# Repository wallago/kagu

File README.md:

# Kagu

A wireless 36-key split keyboard (3x5+3) on the Seeed XIAO nRF52840, running ZMK.

- `keymap.txt`: the keymap, the only file to edit for layout changes
- `keymap/`: the generator that turns it into ZMK, and the diagram
- `config/`: ZMK shields and the generated `kagu.keymap`
- `pcb/`: KiCad projects for both halves
- `case/`: OpenSCAD trays, top plates and Choc v2 keycap risers

## Layout

Colemak-DH, after [dubu36](https://github.com/denniskempin/dubu36). Shortcut modifiers sit on the
home row (pinky to index: Shift, Ctrl, Alt, Super, mirrored). Shift and the layers you use while
writing sit on the thumbs, which keeps hold-tap timing out of the way. Some notes on the layers:

- **rse**: numbers on the left, navigation on the right. **lwr**: symbols.
- **app** and **os**: held from C and `,` (app) or D and H (os). They keep Ctrl or Super down for
  the whole hold, so every key is sent with that modifier, including the arrows on U N E I.
- **sys**: Bluetooth profiles, held from Z or `/`.
- **mou**: held from X. Left-hand Ctrl+Q W S T Z C V for when the right hand is on the mouse.
- **hyp**: held from the right outer thumb. Every key is sent with Ctrl+Alt+Shift+Super, for niri
  bindings. The HYP_[ HYP_\ HYP_] keys on rse send the same.
- Combos: W+F types Esc, and U+Y types Enter.

## Editing the keymap

Each layer is a grid of the 36 keys, laid out as they sit on the board: three rows of ten, then
the six thumbs.

```
layer base: left_mods, right_mods
  Q      W        F      P     B          J        L     U      Y     '
  A      R        S      T     G          M        N     E      I     O
  Z/sys  X/mou    C/app  D/os  V          K        H/os  ,/app  .     \//sys
                  BSPC   LSHFT/LSHFT  lwr/lwr     rse/rse  SPC   _/hyp
```

```
  Z/sys         tap Z, hold the sys layer
  T/LGUI:hm     tap T, hold Super, as a positional home-row mod
  LSHFT/LSHFT   one-shot Shift on tap, plain Shift on hold
  _ / TRNS      nothing / fall through to the layer below
```

Holds shared by several layers are written once as an `overlay` and listed after the layer name.
`layer app + LCTRL` holds Ctrl for as long as the layer is held. Combos are written
`W F -> ESC`. The header of `keymap.txt` covers the details.

After editing, run `just keymap` in the Nix dev shell. It regenerates `kagu.keymap` and redraws
the diagram with [keymap-drawer](https://github.com/caksoylar/keymap-drawer). CI fails if
`kagu.keymap` is out of date.

## Keycaps

- [3dkeycap.com](https://3dkeycap.com)

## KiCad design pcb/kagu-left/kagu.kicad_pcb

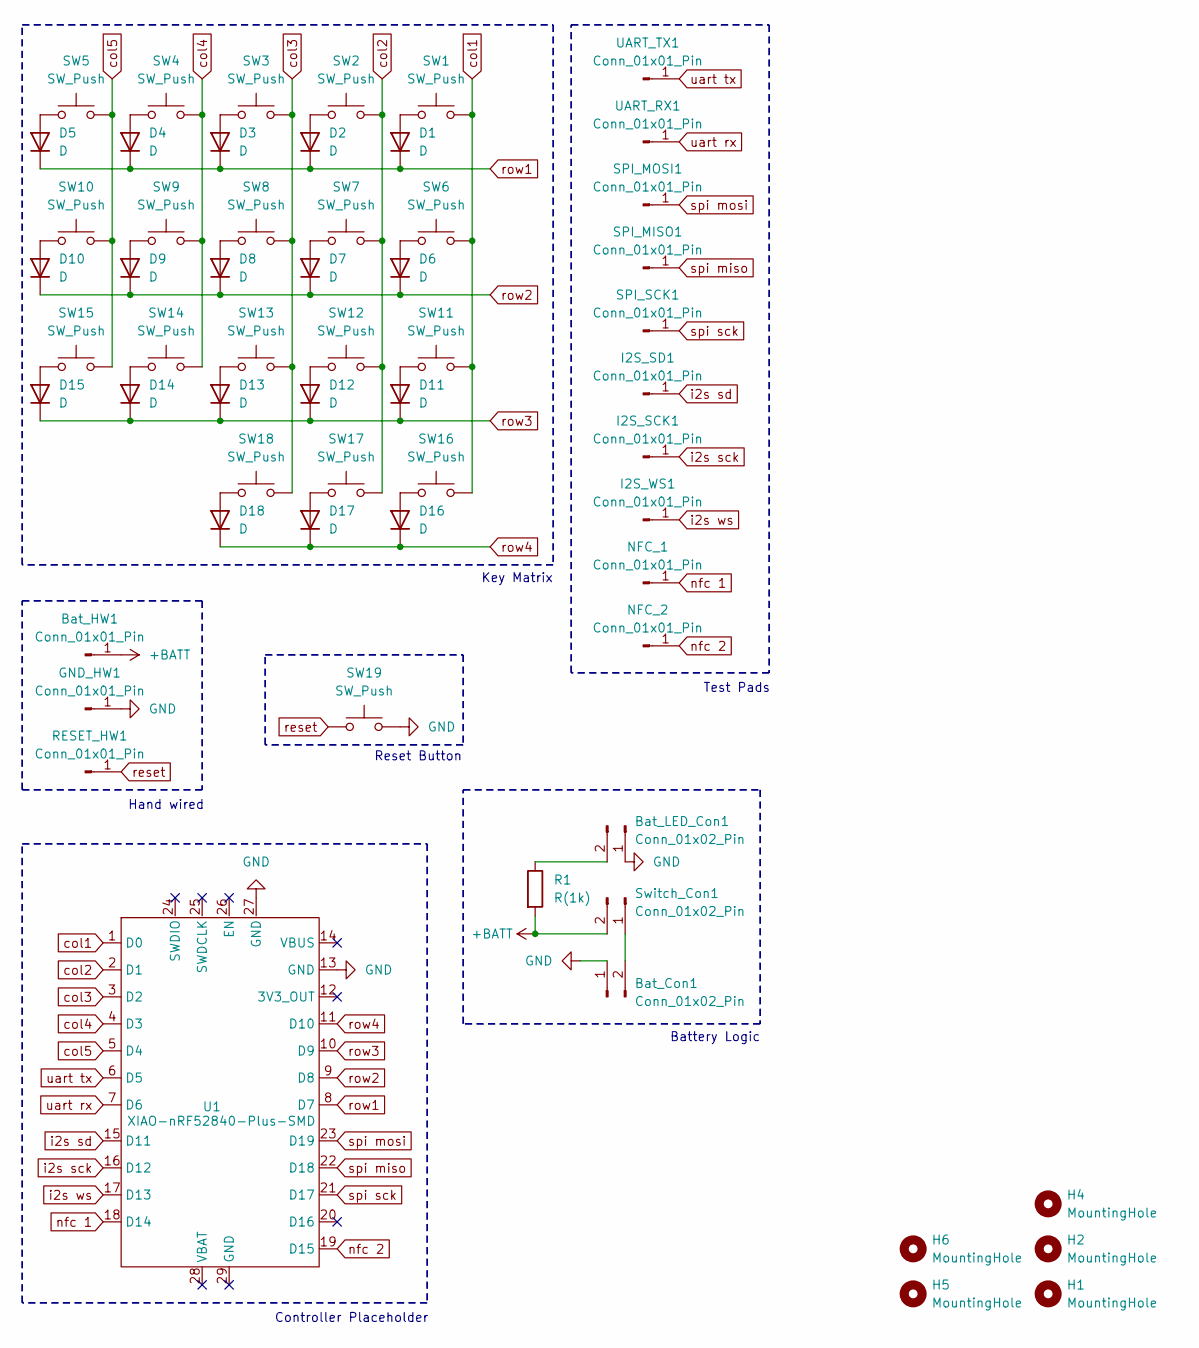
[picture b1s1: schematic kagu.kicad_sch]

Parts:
Bat_Con1: Conn_01x02_Pin; JST_PH_S2B-PH-SM4-TB_1x02-1MP_P2.00mm_Horizontal
Bat_HW1: Conn_01x01_Pin; TestPad
Bat_LED_Con1: Conn_01x02_Pin; JST_SH_SM02B-SRSS-TB_1x02-1MP_P1.00mm_Horizontal
D1, D2, D3, D4, D5, D6, D7, D8, D9, D10, D11, D12, D13, D14, D15, D16, D17, D18: D; D_SOD-123
GND_HW1: Conn_01x01_Pin; TestPad
H1, H2, H4, H5, H6: MountingHole; MountingHole_3.2mm_M3_DIN965_Pad
I2S_SCK1, I2S_SD1, I2S_WS1: Conn_01x01_Pin; TestPad
NFC_1, NFC_2: Conn_01x01_Pin; TestPad
R1: R(1k); R_0805_2012Metric
RESET_HW1: Conn_01x01_Pin; TestPad
SPI_MISO1: Conn_01x01_Pin; TestPad
SPI_MOSI1: Conn_01x01_Pin; TestPad
SPI_SCK1: Conn_01x01_Pin; TestPad
SW1, SW2, SW3, SW4, SW5, SW6, SW7, SW8, SW9, SW10, SW11, SW12, SW13, SW14, SW15, SW16, SW17, SW18: SW_Push; SW_Hotswap_Kailh_Choc_V1V2_Plated
SW19: SW_Push; SW_Push_SPST_NO_Alps_SKRK
Switch_Con1: Conn_01x02_Pin; JST_PH_S2B-PH-SM4-TB_1x02-1MP_P2.00mm_Horizontal
U1: XIAO-nRF52840-Plus-SMD; XIAO-23P-Add-On-Plus
UART_RX1: Conn_01x01_Pin; TestPad
UART_TX1: Conn_01x01_Pin; TestPad

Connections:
+BATT: Bat_HW1.1 (Pin_1_1), R1.2, Switch_Con1.2
GND: Bat_Con1.1, Bat_LED_Con1.1, GND_HW1.1 (Pin_1_1), SW19.2, U1.13 (GND), U1.27 (GND)
unnamed: Bat_Con1.2, Switch_Con1.1
unnamed: Bat_LED_Con1.2, R1.1
unnamed: D1.2 (A), SW1.1
unnamed: D2.2 (A), SW2.1
unnamed: D3.2 (A), SW3.1
unnamed: D4.2 (A), SW4.1
unnamed: D5.2 (A), SW5.1
unnamed: D6.2 (A), SW6.1
unnamed: D7.2 (A), SW7.1
unnamed: D8.2 (A), SW8.1
unnamed: D9.2 (A), SW9.1
unnamed: D10.2 (A), SW10.1
unnamed: D11.2 (A), SW11.1
unnamed: D12.2 (A), SW12.1
unnamed: D13.2 (A), SW13.1
unnamed: D14.2 (A), SW14.1
unnamed: D15.2 (A), SW15.1
unnamed: D16.2 (A), SW16.1
unnamed: D17.2 (A), SW17.1
unnamed: D18.2 (A), SW18.1
col1: SW1.2, SW6.2, SW11.2, SW16.2, U1.1 (D0)
col2: SW2.2, SW7.2, SW12.2, SW17.2, U1.2 (D1)
col3: SW3.2, SW8.2, SW13.2, SW18.2, U1.3 (D2)
col4: SW4.2, SW9.2, SW14.2, U1.4 (D3)
col5: SW5.2, SW10.2, SW15.2, U1.5 (D4)
i2s sck: I2S_SCK1.1 (Pin_1_1), U1.16 (D12)
i2s sd: I2S_SD1.1 (Pin_1_1), U1.15 (D11)
i2s ws: I2S_WS1.1 (Pin_1_1), U1.17 (D13)
nfc 1: NFC_1.1 (Pin_1_1), U1.18 (D14)
nfc 2: NFC_2.1 (Pin_1_1), U1.19 (D15)
reset: RESET_HW1.1 (Pin_1_1), SW19.1
row1: D1.1 (K), D2.1 (K), D3.1 (K), D4.1 (K), D5.1 (K), U1.8 (D7)
row2: D6.1 (K), D7.1 (K), D8.1 (K), D9.1 (K), D10.1 (K), U1.9 (D8)
row3: D11.1 (K), D12.1 (K), D13.1 (K), D14.1 (K), D15.1 (K), U1.10 (D9)
row4: D16.1 (K), D17.1 (K), D18.1 (K), U1.11 (D10)
spi miso: SPI_MISO1.1 (Pin_1_1), U1.22 (D18)
spi mosi: SPI_MOSI1.1 (Pin_1_1), U1.23 (D19)
spi sck: SPI_SCK1.1 (Pin_1_1), U1.21 (D17)
uart rx: U1.7 (D6), UART_RX1.1 (Pin_1_1)
uart tx: U1.6 (D5), UART_TX1.1 (Pin_1_1)

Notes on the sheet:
Reset Button
Key Matrix
Test Pads
Controller Placeholder
Hand wired
Battery Logic

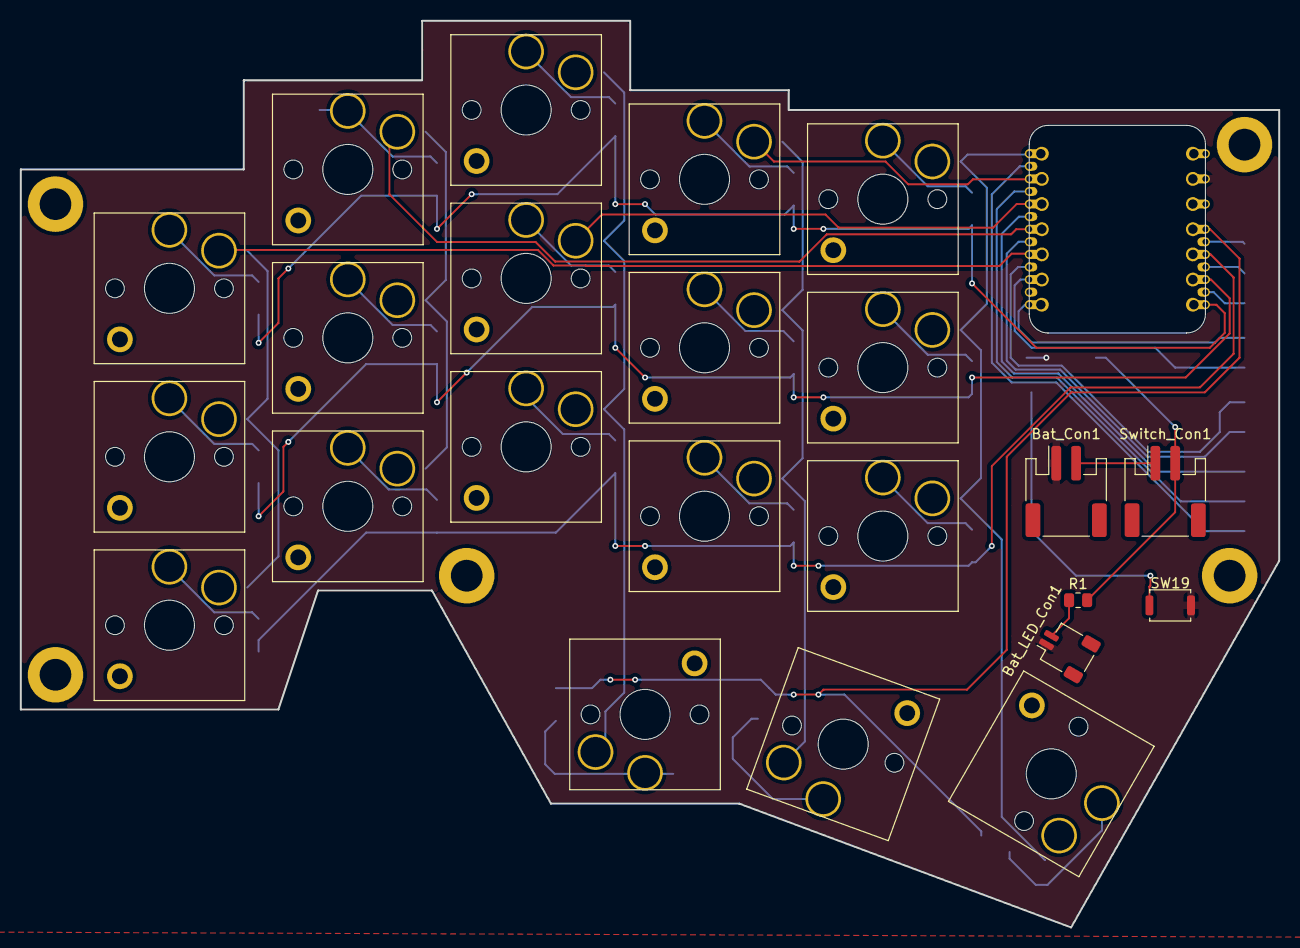
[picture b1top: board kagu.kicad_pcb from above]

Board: 2 copper layers, 127.0 x 91.5 mm, 60 parts (0 on the bottom side), 42 nets.

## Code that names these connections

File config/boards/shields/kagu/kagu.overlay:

#include <dt-bindings/zmk/matrix_transform.h>

/ {
      chosen {
              zmk,kscan = &kscan0;
              zmk,matrix-transform = &default_transform;
      };

      kscan0: kscan {
        compatible = "zmk,kscan-gpio-matrix";
        diode-direction = "col2row";
        wakeup-source;

        col-gpios
          = <&xiao_d 0 GPIO_ACTIVE_HIGH>   // D0  col1
          , <&xiao_d 1 GPIO_ACTIVE_HIGH>   // D1  col2
          , <&xiao_d 2 GPIO_ACTIVE_HIGH>   // D2  col3
          , <&xiao_d 3 GPIO_ACTIVE_HIGH>   // D3  col4
          , <&xiao_d 4 GPIO_ACTIVE_HIGH>   // D4  col5
          ;

        row-gpios
          = <&xiao_d 7 (GPIO_ACTIVE_HIGH | GPIO_PULL_DOWN)>   // D7   row1
          , <&xiao_d 8 (GPIO_ACTIVE_HIGH | GPIO_PULL_DOWN)>   // D8   row2
          , <&xiao_d 9 (GPIO_ACTIVE_HIGH | GPIO_PULL_DOWN)>   // D9   row3
          , <&xiao_d 10 (GPIO_ACTIVE_HIGH | GPIO_PULL_DOWN)>  // D10  row4
          ;
      };

      default_transform: keymap_transform {
        compatible = "zmk,matrix-transform";
        columns = <5>;
        rows = <4>;
        map = <
          RC(0,4) RC(0,3) RC(0,2) RC(0,1) RC(0,0)
          RC(1,4) RC(1,3) RC(1,2) RC(1,1) RC(1,0)
          RC(2,4) RC(2,3) RC(2,2) RC(2,1) RC(2,0)
                          RC(3,2) RC(3,1) RC(3,0)
        >;
      };
};

/* / { */
/*       aliases { */
/*               led-red = &led0; */
/*               led-green = &led1; */
/*               led-blue = &led2; */
/*       }; */
/**/
/*       leds { status = "okay"; }; */
/* }; */

/* &led0 { gpios = <&gpio1 13 GPIO_ACTIVE_HIGH>; };    // D8  = P1.13 */
/* &led1 { gpios = <&gpio1 14 GPIO_ACTIVE_HIGH>; };    // D9  = P1.14 */
/* &led2 { gpios = <&gpio1 15 GPIO_ACTIVE_HIGH>; };    // D10 = P1.15 */
